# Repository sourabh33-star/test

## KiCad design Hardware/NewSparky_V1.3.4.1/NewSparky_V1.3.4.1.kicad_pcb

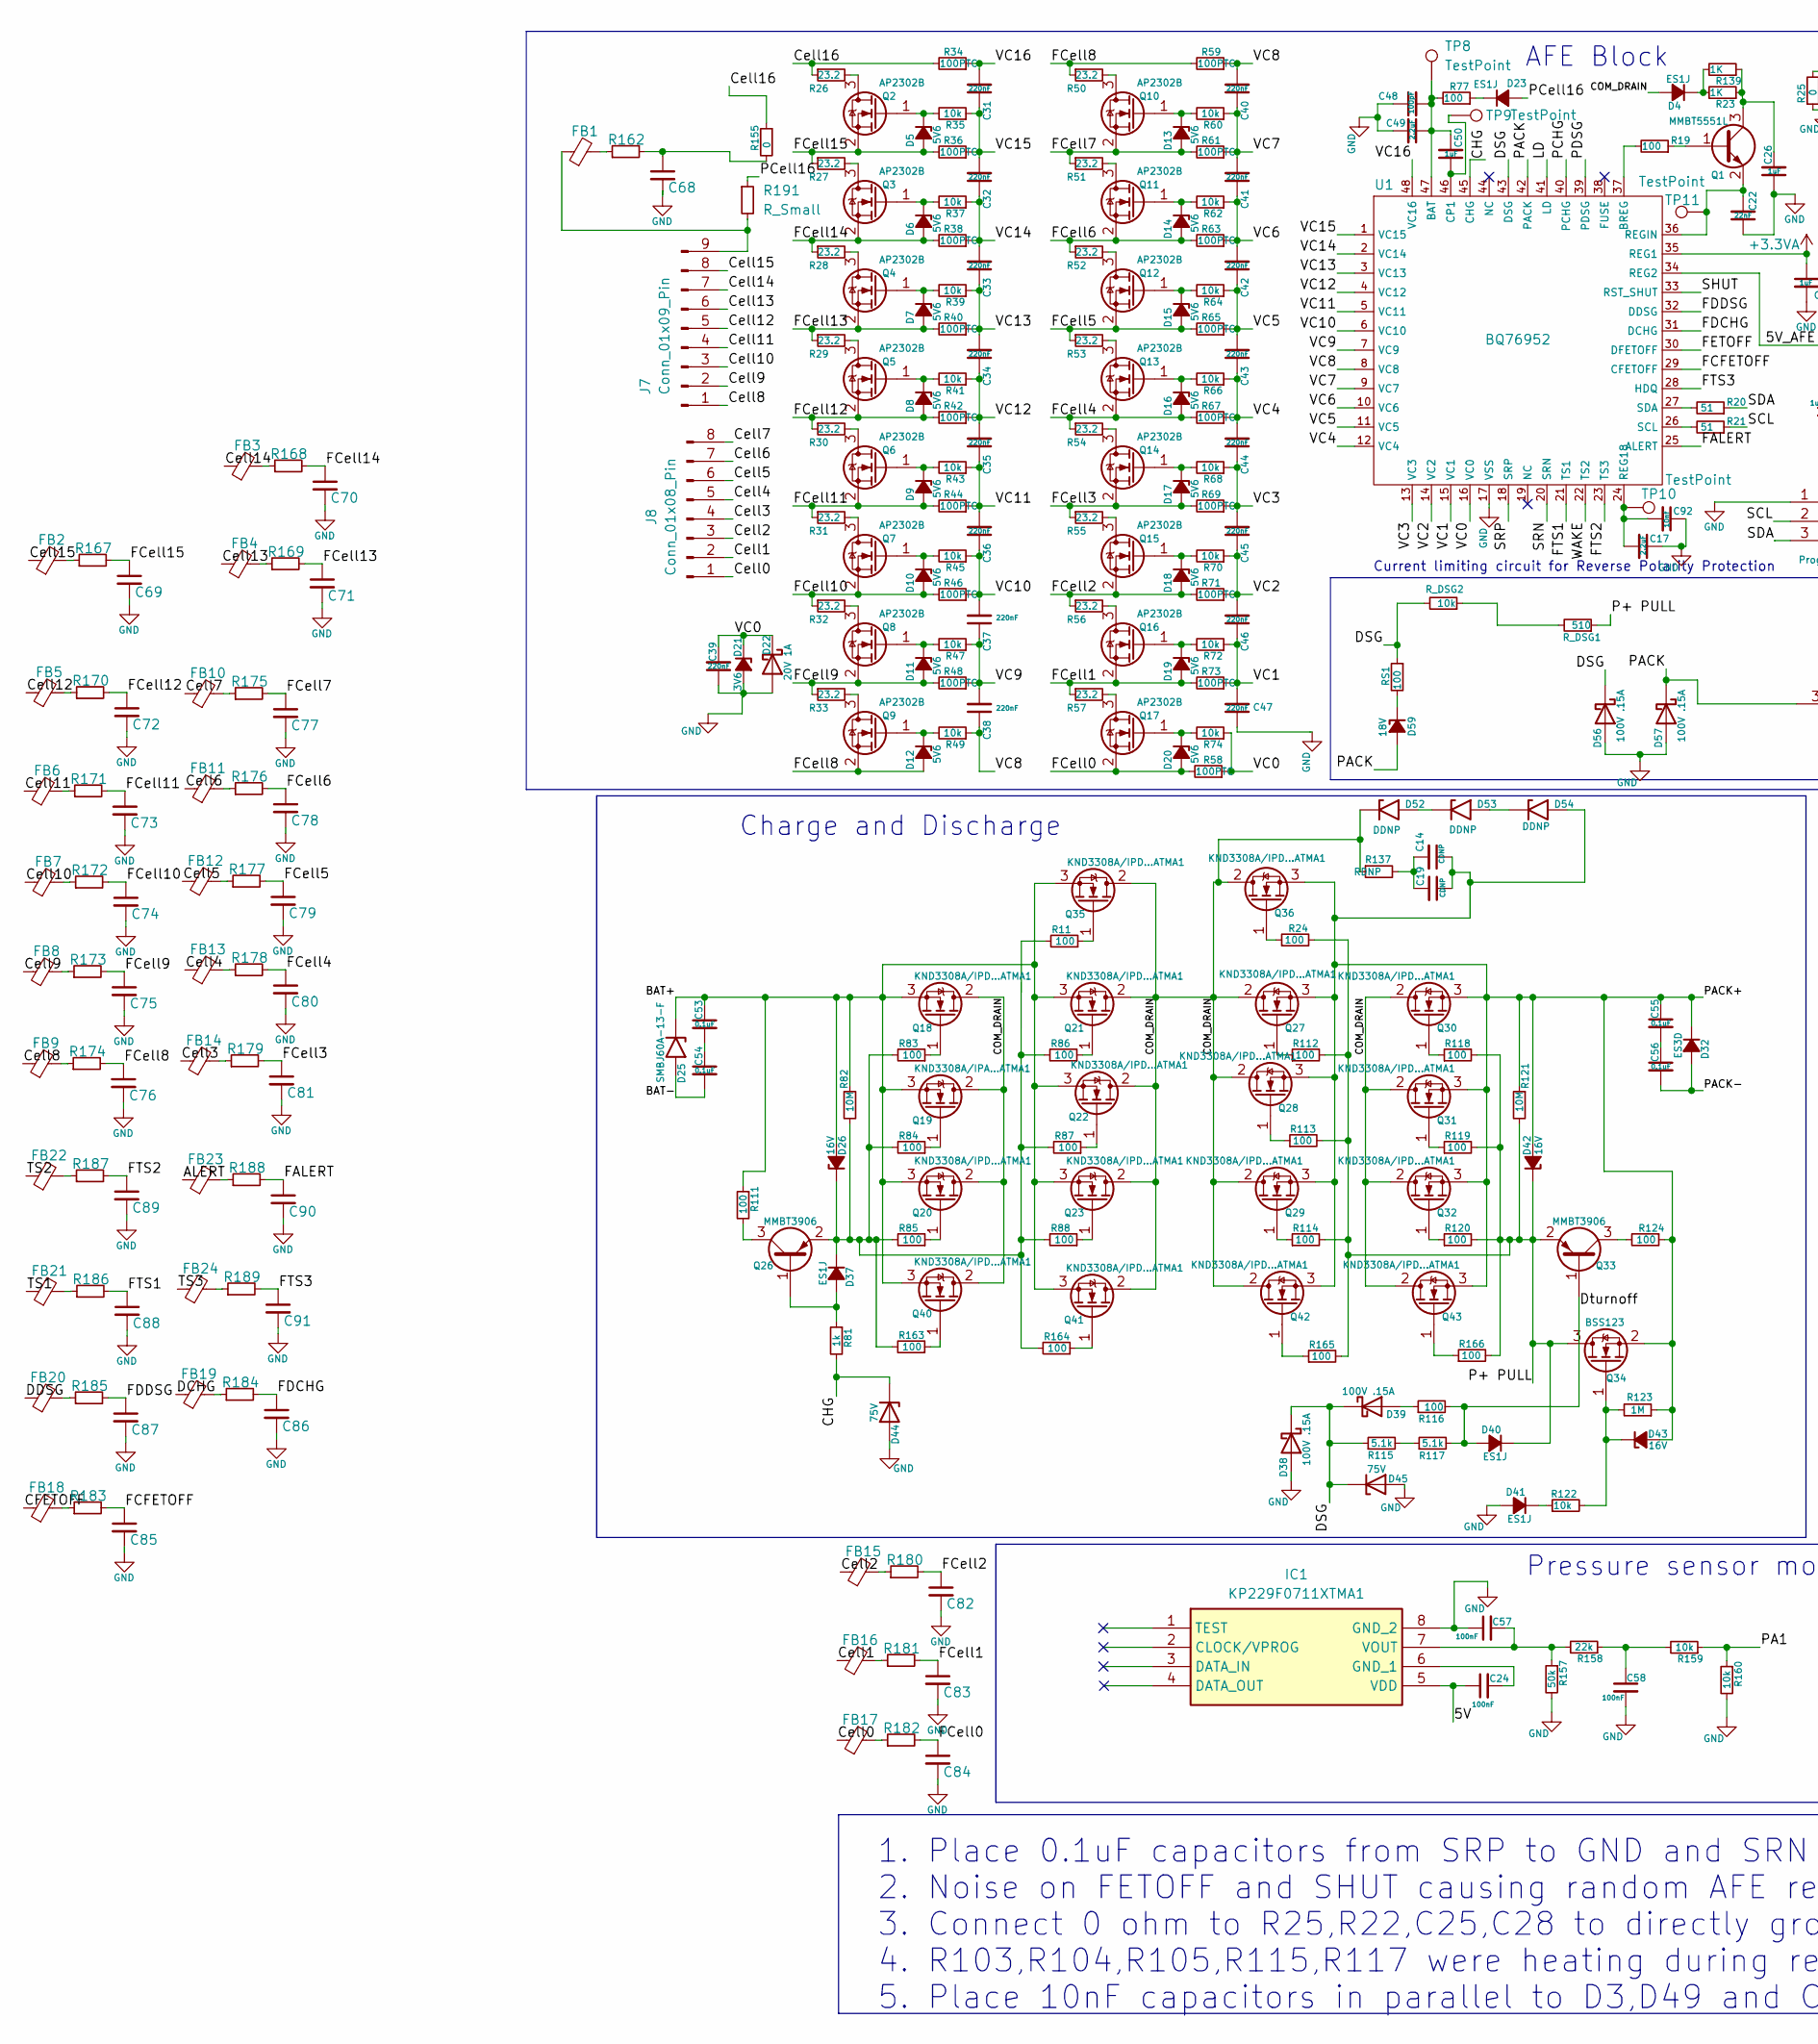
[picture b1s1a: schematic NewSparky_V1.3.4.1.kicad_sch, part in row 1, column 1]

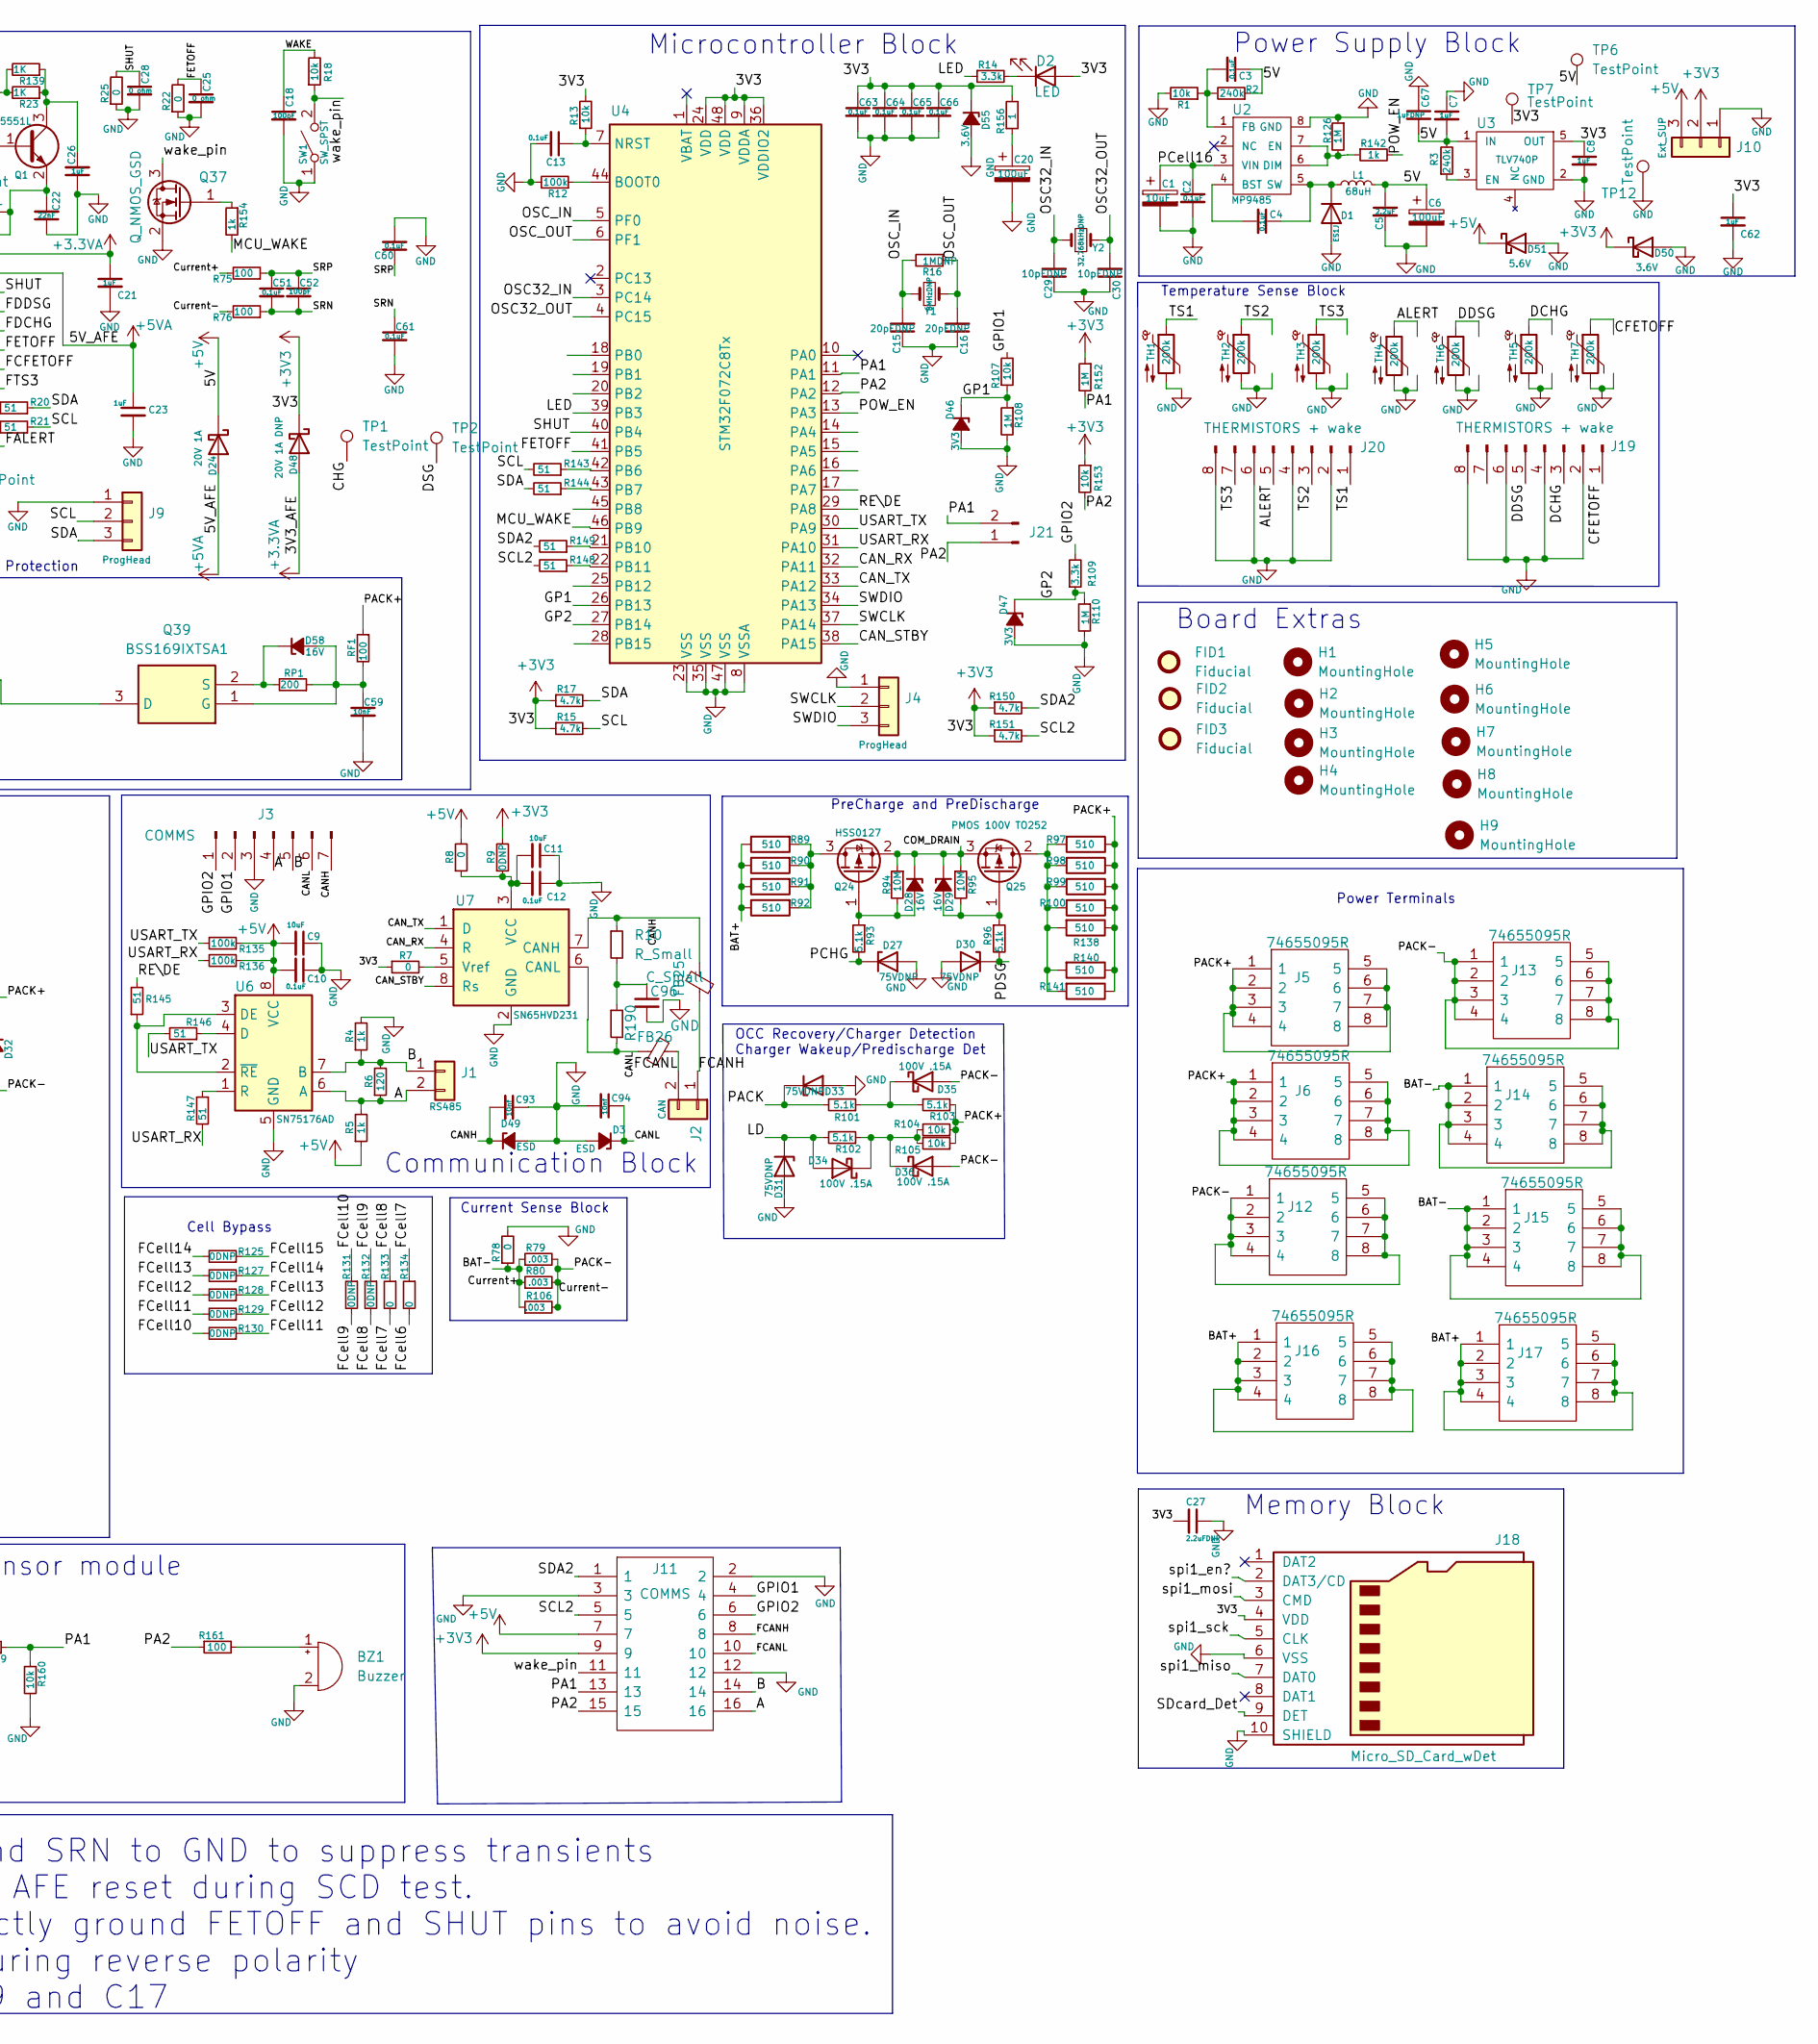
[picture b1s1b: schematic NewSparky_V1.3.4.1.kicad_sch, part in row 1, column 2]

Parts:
BZ1: Buzzer; Buzzer_12x9.5RM7.6
C1: 10uF
C2, C3, C4, C10, C12, C13, C51, C53, C54, C55, C56, C60, C61, C63, C64, C65, C66: 0.1uF; C_0603_1608Metric
C5, C17: 2.2uF; C_0603_1608Metric
C6, C20: 100uF; CP_Radial_D5.0mm_P2.00mm
C7, C8, C21, C23, C62: 1uF; C_0603_1608Metric
C9, C11: 10uF; C_0603_1608Metric
C14, C19: CDNP; C_1206_3216Metric
C15, C16: 20pFDNP; C_0603_1608Metric
C18, C48, C52: 100pF; C_0603_1608Metric
C22: 22nF; C_0603_1608Metric
C24, C57, C58: 100nF; C_0603_1608Metric
C25, C28: 0 ohm; C_0603_1608Metric
C26, C50: 1uF; C_1206_3216Metric
C27: 2.2uFDNP; C_1206_3216Metric
C29, C30: 10pFDNP; C_0603_1608Metric
C31, C32, C33, C34, C35, C36, C37, C38, C39, C40, C41, C42, C43, C44, C45, C46, C47: 220nF; C_0603_1608Metric
C49: 2.2uF; C_1206_3216Metric
C59: 10nF; C_0603_1608Metric
C67: 1uFDNP; C_0603_1608Metric
C68, C69, C70, C71, C72, C73, C74, C75, C76, C77, C78, C79, C80, C81, C82, C83, C84, C96: C_Small; C_0603_1608Metric
C85, C86, C87, C88, C89, C90, C91: C_Small; C_1206_3216Metric
C92, C93, C94: 10nf; C_0603_1608Metric
D1, D4, D23, D37, D40, D41: ES1J; D_SOD-123
D2: LED; LED_0603_1608Metric
D3, D49: ESD; D_SOD-523
D5, D6, D7, D8, D9, D10, D11, D12, D13, D14, D15, D16, D17, D18, D19, D20: 5V6; D_SOD-323
D21: 3V6; D_SOD-323
D22, D24: 20V 1A; D_SOD-123
D25: SMBJ60A-13-F; D_SMC
D26, D28, D29, D42, D43, D58: 16V; D_SOD-123
D27, D30, D31, D33: 75VDNP; D_SOD-123
D32: ES3D; D_SMC
D34, D35, D36, D38, D39, D56, D57: 100V .15A; D_SOD-123
D44, D45: 75V; D_SOD-123
D46, D47: 3V3; D_SOD-323
D48: 20V 1A DNP; D_SOD-123
D50, D55: 3.6V; D_SOD-123
D51: 5.6V; D_SOD-123
D52, D53, D54: DDNP; D_SMA
D59: 18V; D_SOD-123
FB1, FB2, FB3, FB4, FB5, FB6, FB7, FB8, FB9, FB10, FB11, FB12, FB13, FB14, FB15, FB16, FB17, FB18, FB19, FB20, FB21, FB22, FB23, FB24, FB25, FB26: FerriteBead_Small; L_0603_1608Metric
FID1, FID2, FID3: Fiducial; Fiducial_1mm_Mask2mm
H1, H2, H3, H4, H5, H6, H7, H8, H9: MountingHole; MountingHole_3.2mm_M3_DIN965
IC1: KP229F0711XTMA1; Manufacturer_Part_Number KP229F0711XTMA1; Mouser Part Number 726-KP229F0711XTMA1
J1: RS485; JST_XH_S2B-XH-A-1_1x02_P2.50mm_Horizontal
J2: CAN; JST_XH_S2B-XH-A-1_1x02_P2.50mm_Horizontal
J3: COMMS; JST_XH_S7B-XH-A-1_1x07_P2.50mm_Horizontal
J4, J9: ProgHead; PinHeader_1x03_P2.54mm_Vertical
J5, J6, J12, J13, J14, J15, J16, J17: 74655095R; Manufacturer_Part_Number 74650094; Mouser Part Number 710-74650094
J7: Conn_01x09_Pin; 559350910
J8: Conn_01x08_Pin; 559350810
J10: Ext_SUP; PinHeader_1x03_P2.54mm_Vertical
J11: COMMS; S16BPUDSS1LFSN; Manufacturer_Part_Number 501876-1640; Mouser Part Number 538-501876-1640
J18: Micro_SD_Card_wDet; SHOU HAN TF PUSH
J19, J20: THERMISTORS + wake; CONN_S08B-PUDSS-1_JST
J21: Conn_01x02_Pin; PinSocket_1x02_P2.54mm_Vertical
L1: 68uH; L_Taiyo-Yuden_NR-40xx
Q1: MMBT5551L; SOT-23
Q2, Q3, Q4, Q5, Q6, Q7, Q8, Q9, Q10, Q11, Q12, Q13, Q14, Q15, Q16, Q17: AP2302B; SOT-23
Q18, Q20, Q21, Q22, Q23, Q27, Q28, Q29, Q30, Q31, Q32, Q35, Q36, Q40, Q41, Q42, Q43: KND3308A/IPD...ATMA1; TO-252-2
Q19: KND3308A/IPA...ATMA1; TO-252-2
Q24: HSS0127; SOT-23
Q25: PMOS 100V TO252; TO-252-2
Q26, Q33: MMBT3906; SOT-23
Q34: BSS123; SOT-23
Q37: Q_NMOS_GSD; SOT-23
Q39: BSS169IXTSA1; SOT95P237X112-3N; Manufacturer_Part_Number BSS169IXTSA1; Mouser Part Number 726-BSS169IXTSA1
R1, R13, R18, R35, R37, R39, R41, R43, R45, R47, R49, R60, R62, R64, R66, R68, R70, R72, R74, R107, R122, R153, R159, R160: 10k; R_0603_1608Metric
R2, R3: 240k; R_0603_1608Metric
R4, R5, R81, R142, R154: 1k; R_0603_1608Metric
R6: 120; R_0603_1608Metric
R7, R8, R22, R25, R133, R134, R155: 0; R_0603_1608Metric
R9, R125, R127, R128, R129, R130, R131, R132: 0DNP; R_0603_1608Metric
R10, R162, R167, R168, R169, R170, R171, R172, R173, R174, R175, R176, R177, R178, R179, R180, R181, R182, R183, R184, R185, R186, R187, R188, R189, R190, R191: R_Small; R_0603_1608Metric
R11, R19, R24, R75, R76, R77, R83, R84, R85, R86, R87, R88, R111, R112, R113, R114, R116, R118, R119, R120, R124, R161, R163, R164, R165, R166: 100; R_0603_1608Metric
R12, R135, R136: 100k; R_0603_1608Metric
R14, R109: 3.3k; R_0603_1608Metric
R15, R17, R150, R151: 4.7k; R_0603_1608Metric
R16: 1MDNP; R_0603_1608Metric
R20, R21, R143, R144, R145, R146, R147, R148, R149: 51; R_0603_1608Metric
R23, R139: 1K; R_1206_3216Metric
R26, R27, R28, R29, R30, R31, R32, R33, R50, R51, R52, R53, R54, R55, R56, R57: 23.2; R_2512_6332Metric
R34, R36, R38, R40, R42, R44, R46, R48, R58, R59, R61, R63, R65, R67, R69, R71, R73: 100PTC; R_0603_1608Metric
R78: 0; R_1206_3216Metric
R79, R80, R106: .003; RESC15078X50N
R82, R94, R95, R121: 10M; R_0603_1608Metric
R89, R90, R91, R92, R97, R98, R99, R100, R138, R140, R141: 510; R_2512_6332Metric_Pad1.40x3.35mm_HandSolder
R93, R96, R101, R102: 5.1k; R_0603_1608Metric
R103, R115, R117: 5.1k; R_1206_3216Metric
R104, R105: 10k; R_1206_3216Metric
R108, R110, R123, R126, R152: 1M; R_0603_1608Metric
R137: RDNP; R_1206_3216Metric
R156: 1; R_0603_1608Metric
R157: 50k; R_0603_1608Metric
R158: 22k; R_0603_1608Metric
RF1: 100; R_0603_1608Metric
RP1: 200; R_0603_1608Metric
RS1: 100; R_0603_1608Metric
R_DSG1: 510; R_1206_3216Metric
R_DSG2: 10k; R_1206_3216Metric
SW1: SW_SPST; PinHeader_1x02_P2.54mm_Vertical
TH1, TH2, TH3, TH4, TH5, TH6, TH7: 200k; JST_EH_S2B-EH_1x02_P2.50mm_Horizontal
TP1, TP2: TestPoint; TestPoint_THTPad_1.0x1.0mm_Drill0.5mm
TP6, TP7, TP8, TP9, TP10, TP11, TP12: TestPoint; TestPoint_THTPad_2.0x2.0mm_Drill1.0mm
U1: BQ76952; QFP50P900X900X120-48N
U2: MP9485; SOIC-8-1EP_3.9x4.9mm_P1.27mm_EP2.41x3.3mm
U3: TLV740P; SOT-23-5
U4: STM32F072C8Tx; QFP50P900X900X160-48N
U6: SN75176AD; SOIC-8_3.9x4.9mm_P1.27mm
U7: SN65HVD231; SOIC-8_3.9x4.9mm_P1.27mm
Y1: 8MHzDNP; Crystal_SMD_HC49-SD
Y2: 32.768kHzDNP; Crystal_Round_D3.0mm_Vertical

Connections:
+3.3VA: C21.1, D48.2 (A), U1.35 (REG1)
+3V3: C8.1, C27.2, C62.1, C63.1, C64.1, C65.1, C66.1, D2.2 (A), D48.1 (K), D50.1 (K), D55.1 (K), J10.2, J11.9, J18.4 (VDD), R7.1, R9.2, R13.2, R15.1, R17.1, R150.1, R151.1, R152.1, R153.1, R156.2, TP7.1, U3.5 (OUT), U4.9 (VDDA), U4.24 (VDD), U4.36 (VDDIO2), U4.48 (VDD)
+5V: C3.1, C5.1, C6.1, C7.2, C9.2, C10.2, C24.1, C67.2, D24.1 (K), D51.1 (K), IC1.5 (VDD), J10.3, J11.7, L1.2, R2.1, R3.2, R5.1, R8.2, R135.1, R136.1, TP6.1, U3.1 (IN), U6.8 (VCC)
+5VA: C23.1, D24.2 (A), U1.34 (REG2)
/A: J1.2, J3.4, J11.16, R5.2, R6.1, U6.6 (A)
/ALERT: FB23.1, J20.5, TH4.1
/B: J1.1, J3.5, J11.14, R4.1, R6.2, U6.7 (B)
/BAT+: C53.1, D25.1 (A1), D26.2 (A), J16.1, J16.2, J16.3, J16.4, J16.5, J16.6, J16.7, J16.8, J17.1, J17.2, J17.3, J17.4, J17.5, J17.6, J17.7, J17.8, Q18.3 (S), Q19.3 (S), Q20.3 (S), Q21.3 (S), Q22.3 (S), Q23.3 (S), Q35.3 (S), Q40.3 (S), Q41.3 (S), R82.1, R89.1, R90.1, R91.1, R92.1, R111.1; also elsewhere on the board
/CANH: C93.2, D49.1 (K), FB25.2, J3.7, R10.1, U7.7 (CANH)
/CANL: C94.1, D3.1 (K), FB26.2, J3.6, R190.2, U7.6 (CANL)
/CAN_RX: U4.32 (PA11), U7.4 (R)
/CAN_STBY: U4.38 (PA15), U7.8 (Rs)
/CAN_TX: U4.33 (PA12), U7.1 (D)
/CFETOFF: FB18.1, J19.1, TH7.1
/CHG: D44.1 (K), R81.2, TP1.1, U1.45 (CHG)
/COM_DRAIN: D4.2 (A), D28.1 (K), D29.1 (K), D52.1 (A1), Q18.2 (D), Q19.2 (D), Q20.2 (D), Q21.2 (D), Q22.2 (D), Q23.2 (D), Q24.2 (S), Q25.3 (S), Q27.2 (D), Q28.2 (D), Q29.2 (D), Q30.2 (D), Q31.2 (D), Q32.2 (D), Q35.2 (D), Q36.2 (D), Q40.2 (D), Q41.2 (D), Q42.2 (D), Q43.2 (D), R94.1, R95.1, R137.1
/Cell0: FB17.1, J8.1
/Cell1: FB16.1, J8.2
/Cell2: FB15.1, J8.3
/Cell3: FB14.1, J8.4
/Cell4: FB13.1, J8.5
/Cell5: FB12.1, J8.6
/Cell6: FB11.1, J8.7
/Cell7: FB10.1, J8.8
/Cell8: FB9.1, J7.1
/Cell9: FB8.1, J7.2
/Cell10: FB7.1, J7.3
/Cell11: FB6.1, J7.4
/Cell12: FB5.1, J7.5
/Cell13: FB4.1, J7.6
/Cell14: FB3.1, J7.7
/Cell15: FB2.1, J7.8
/Cell16: R26.1, R34.2, R155.1
/DCHG: FB19.1, J19.3, TH5.1
/DDSG: FB20.1, J19.5, TH6.1
/DSG: D38.1 (K), D39.1 (K), D45.1 (K), D56.1 (K), R115.1, RS1.1, R_DSG2.2, TP2.1, U1.43 (DSG)
/Dturnoff: D40.2 (A), Q33.1 (B), R116.2, R117.2
/FALERT: C90.1, R188.2, U1.25 (ALERT)
/FCANH: FB25.1, J2.1, J11.8
/FCANL: FB26.1, J2.2, J11.10
/FCFETOFF: C85.1, R183.2, U1.29 (CFETOFF)
/FCell0: C84.1, D20.2 (A), Q17.2 (S), R58.2, R182.2
/FCell1: C83.1, D19.2 (A), Q16.2 (S), R57.1, R73.2, R181.2
/FCell2: C82.1, D18.2 (A), Q15.2 (S), R56.1, R71.2, R180.2
/FCell3: C81.1, D17.2 (A), Q14.2 (S), R55.1, R69.2, R179.2
/FCell4: C80.1, D16.2 (A), Q13.2 (S), R54.1, R67.2, R178.2
/FCell5: C79.1, D15.2 (A), Q12.2 (S), R53.1, R65.2, R177.2
/FCell6: C78.1, D14.2 (A), Q11.2 (S), R52.1, R63.2, R134.2, R176.2
/FCell7: C77.1, D13.2 (A), Q10.2 (S), R51.1, R61.2, R133.2, R134.1, R175.2
/FCell8: C76.1, D12.2 (A), Q9.2 (S), R50.1, R59.2, R132.2, R133.1, R174.2
/FCell9: C75.1, D11.2 (A), Q8.2 (S), R33.1, R48.2, R131.2, R132.1, R173.2
/FCell10: C74.1, D10.2 (A), Q7.2 (S), R32.1, R46.2, R130.2, R131.1, R172.2
/FCell11: C73.1, D9.2 (A), Q6.2 (S), R31.1, R44.2, R129.2, R130.1, R171.2
/FCell12: C72.1, D8.2 (A), Q5.2 (S), R30.1, R42.2, R128.2, R129.1, R170.2
/FCell13: C71.1, D7.2 (A), Q4.2 (S), R29.1, R40.2, R127.2, R128.1, R169.2
/FCell14: C70.1, D6.2 (A), Q3.2 (S), R28.1, R38.2, R125.2, R127.1, R168.2
/FCell15: C69.1, D5.2 (A), Q2.2 (S), R27.1, R36.2, R125.1, R167.2
/FDCHG: C86.1, R184.2, U1.31 (DCHG)
/FDDSG: C87.1, R185.2, U1.32 (DDSG)
/FETOFF: C25.1, R22.2, U1.30 (DFETOFF), U4.41 (PB5)
/FTS1: C88.1, R186.2, U1.21 (TS1)
/FTS2: C89.1, R187.2, U1.23 (TS3)
/FTS3: C91.1, R189.2, U1.28 (HDQ)
/GP1: D46.1 (K), R107.1, R108.1, U4.26 (PB13)
/GP2: D47.1 (K), R109.1, R110.1, U4.27 (PB14)
/GPIO1: J3.2, J11.4, R107.2
/GPIO2: J3.1, J11.6, R109.2
/LD: D31.1 (K), D34.2 (A), R102.2, U1.41 (LD)
/LED: R14.1, U4.39 (PB3)
/MCU_WAKE: R154.2, U4.46 (PB9)
/OSC32_IN: C29.2, U4.3 (PC14), Y2.1
/OSC32_OUT: C30.2, U4.4 (PC15), Y2.2
/OSC_IN: C15.2, R16.2, U4.5 (PF0), Y1.1
/OSC_OUT: C16.2, R16.1, U4.6 (PF1), Y1.2
/P+ PULL: D40.1 (K), D42.1 (K), Q33.2 (E), Q34.3 (D), R24.2, R112.2, R113.2, R114.2, R118.2, R119.2, R120.2, R121.2, R165.2, R166.2, R_DSG1.1
/PA1: J11.13, J21.2, R152.2, R159.1, R160.1, U4.11 (PA1)
/PA2: J11.15, J21.1, R153.2, R161.1, U4.12 (PA2)
/PACK: D33.1 (K), D57.1 (K), D59.2 (A), Q39.3 (D), R101.2, U1.42 (PACK)
/PACK+: C14.1, C19.1, C55.1, D32.1 (K), D42.2 (A), D43.2 (A), D54.2 (A2), J5.1, J5.2, J5.3, J5.4, J5.5, J5.6, J5.7, J5.8, J6.1, J6.2, J6.3, J6.4, J6.5, J6.6, J6.7, J6.8, Q27.3 (S), Q28.3 (S), Q29.3 (S), Q30.3 (S), Q31.3 (S), Q32.3 (S), Q34.2 (S), Q36.3 (S), Q42.3 (S), Q43.3 (S), R97.1, R98.1, R99.1, R100.1, R103.1, R104.1, R105.1, R121.1, R123.1, R124.1, R138.1, R140.1, R141.1, RF1.1
/PCHG: D27.1 (K), R93.2, U1.40 (PCHG)
/PCell16: C1.1, C2.1, D23.2 (A), R191.1, U2.3 (VIN)
/PDSG: D30.1 (K), R96.2, U1.39 (PDSG)
/POW_EN: R142.2, U4.13 (PA3)
/RE\DE: R145.2, U4.29 (PA8)
/SCL: J9.2, R15.2, R21.1, R143.2
/SCL2: J11.5, R148.2, R151.2
/SDA: J9.3, R17.2, R20.1, R144.2
/SDA2: J11.1, R149.2, R150.2
/SDcard_Det: J18.9 (DET)
/SHUT: C28.1, R25.2, U1.33 (RST_SHUT), U4.40 (PB4)
/SRN: C51.2, C52.2, C61.1, R76.1, U1.20 (SRN)
/SRP: C51.1, C52.1, C60.1, R75.1, U1.18 (SRP)
/SWCLK: J4.2, U4.37 (PA14)
/SWDIO: J4.3, U4.34 (PA13)
/TS1: FB21.1, J20.1, TH1.1
/TS2: FB22.1, J20.3, TH2.1
/TS3: FB24.1, J20.7, TH3.1
/USART_RX: R136.2, R147.2, U4.31 (PA10)
/USART_TX: R135.2, R146.2, U4.30 (PA9)
/VC0: C39.2, D21.1 (K), D22.1 (K), R58.1, R74.1, U1.16 (VC0)
/VC1: C46.1, C47.2, R72.1, R73.1, U1.15 (VC1)
/VC2: C45.1, C46.2, R70.1, R71.1, U1.14 (VC2)
/VC3: C44.1, C45.2, R68.1, R69.1, U1.13 (VC3)
/VC4: C43.1, C44.2, R66.1, R67.1, U1.12 (VC4)
/VC5: C42.1, C43.2, R64.1, R65.1, U1.11 (VC5)
/VC6: C41.1, C42.2, R62.1, R63.1, U1.10 (VC6)
/VC7: C40.1, C41.2, R60.1, R61.1, U1.9 (VC7)
/VC8: C38.1, C40.2, R49.1, R59.1, U1.8 (VC8)
/VC9: C37.1, C38.2, R47.1, R48.1, U1.7 (VC9)
/VC10: C36.1, C37.2, R45.1, R46.1, U1.6 (VC10)
/VC11: C35.1, C36.2, R43.1, R44.1, U1.5 (VC11)
/VC12: C34.1, C35.2, R41.1, R42.1, U1.4 (VC12)
/VC13: C33.1, C34.2, R39.1, R40.1, U1.3 (VC13)
/VC14: C32.1, C33.2, R37.1, R38.1, U1.2 (VC14)
/VC15: C31.1, C32.2, R35.1, R36.1, U1.1 (VC15)
/VC16: C31.2, R34.1, U1.48 (VC16)
/WAKE: C18.1, R18.2, U1.22 (TS2)
/spi1_en?: J18.2 (DAT3/CD)
/spi1_miso: J18.7 (DAT0)
/spi1_mosi: J18.3 (CMD)
/spi1_sck: J18.5 (CLK)
/wake_pin: J11.11, Q37.3 (D), R18.1, SW1.2 (B)
GND: BZ1.2 (+), C1.2, C2.2, C5.2, C6.2, C7.1, C8.2, C9.1, C10.1, C11.1, C12.1, C13.2, C15.1, C16.1, C17.1, C18.2, C20.2, C21.2, C22.1, C23.2, C25.2, C26.1, C27.1, C28.2, C29.1, C30.1, C39.1, C47.1, C48.1, C49.2, C57.1, C58.2, C59.2, C60.2, C61.2, C62.2, C63.2, C64.2, C65.2, C66.2, C67.1, C68.2, C69.2, C70.2, C71.2, C72.2, C73.2, C74.2, C75.2, C76.2, C77.2, C78.2, C79.2, C80.2, C81.2, C82.2, C83.2, C84.2, C85.2, C86.2, C87.2, C88.2, C89.2, C90.2, C91.2, C92.1, C93.1, C94.2, C96.2, D1.2 (A), D3.2 (A), D21.2 (A), D22.2 (A), D27.2 (A), D30.2 (A), D31.2 (A), D33.2 (A), D38.2 (A), D41.2 (A), D44.2 (A), D45.2 (A), D46.2 (A), D47.2 (A), D49.2 (A), D50.2 (A), D51.2 (A), D55.2 (A), D56.2 (A), D57.2 (A), IC1.8 (GND_2), J3.3, J4.1, J9.1, J10.1, J11.2, J11.3, J11.12, J18.6 (VSS), J18.10 (SHIELD), J19.2, J19.4, J19.6, J19.8, J20.2, J20.4, J20.6, J20.8, Q37.2 (S), R1.2, R4.2, R12.2, R22.1, R25.1, R78.2, R108.2, R110.2, R126.1, R157.2, R160.2, SW1.1 (A), TH1.2, TH2.2, TH3.2, TH4.2, TH5.2, TH6.2, TH7.2, TP12.1, U1.17 (VSS), U2.8 (GND), U2.9 (GND), U3.2 (GND), U4.8 (VSSA), U4.23 (VSS), U4.35 (VSS), U4.47 (VSS), U6.5 (GND), U7.2 (GND)
unnamed: BZ1.1 (-), R161.2
unnamed: C14.2, C19.2, R137.2
unnamed: C20.1, R156.1
unnamed: C53.2, C54.1
unnamed: C55.2, C56.1
unnamed: C58.1, R158.1, R159.2
unnamed: C68.1, R155.2, R162.2
unnamed: C96.1, R10.2, R190.1
unnamed: C4.1, D1.1 (K), L1.1, U2.5 (SW)
unnamed: D2.1 (K), R14.2
unnamed: D4.1 (K), R23.2, R139.2
unnamed: D5.1 (K), Q2.1 (G), R35.2
unnamed: D6.1 (K), Q3.1 (G), R37.2
unnamed: D7.1 (K), Q4.1 (G), R39.2
unnamed: D8.1 (K), Q5.1 (G), R41.2
unnamed: D9.1 (K), Q6.1 (G), R43.2
unnamed: D10.1 (K), Q7.1 (G), R45.2
unnamed: D11.1 (K), Q8.1 (G), R47.2
unnamed: D12.1 (K), Q9.1 (G), R49.2
unnamed: D13.1 (K), Q10.1 (G), R60.2
unnamed: D14.1 (K), Q11.1 (G), R62.2
unnamed: D15.1 (K), Q12.1 (G), R64.2
unnamed: D16.1 (K), Q13.1 (G), R66.2
unnamed: D17.1 (K), Q14.1 (G), R68.2
unnamed: D18.1 (K), Q15.1 (G), R70.2
unnamed: D19.1 (K), Q16.1 (G), R72.2
unnamed: D20.1 (K), Q17.1 (G), R74.2
unnamed: D23.1 (K), R77.1
unnamed: D26.1 (K), D37.1 (K), Q26.2 (E), R11.2, R82.2, R83.2, R84.2, R85.2, R86.2, R87.2, R88.2, R163.2, R164.2
unnamed: D29.2 (A), Q25.1 (G), R95.2, R96.1
unnamed: D34.1 (K), D36.1 (K), R102.1, R104.2, R105.2
unnamed: D35.1 (K), R101.1, R103.2
unnamed: D37.2 (A), Q26.1 (B), R81.1
unnamed: D39.2 (A), R116.1
unnamed: D41.1 (K), R122.1
unnamed: D43.1 (K), Q34.1 (G), R122.2, R123.2
unnamed: D52.2 (A2), D53.1 (A1)
unnamed: D53.2 (A2), D54.1 (A1)
unnamed: C59.1, D58.2 (A), Q39.1 (G), RF1.2, RP1.1
unnamed: D58.1 (K), Q39.2 (S), RP1.2
unnamed: D59.1 (K), RS1.2
unnamed: FB1.2, R162.1
unnamed: FB2.2, R167.1
unnamed: FB3.2, R168.1
unnamed: FB4.2, R169.1
unnamed: FB5.2, R170.1
unnamed: FB6.2, R171.1
unnamed: FB7.2, R172.1
unnamed: FB8.2, R173.1
unnamed: FB9.2, R174.1
unnamed: FB10.2, R175.1
unnamed: FB11.2, R176.1
unnamed: FB12.2, R177.1
unnamed: FB13.2, R178.1
unnamed: FB14.2, R179.1
unnamed: FB15.2, R180.1
unnamed: FB16.2, R181.1
unnamed: FB17.2, R182.1
unnamed: FB18.2, R183.1
unnamed: FB19.2, R184.1
unnamed: FB20.2, R185.1
unnamed: FB21.2, R186.1
unnamed: FB22.2, R187.1
unnamed: FB23.2, R188.1
unnamed: FB24.2, R189.1
unnamed: C24.2, IC1.6 (GND_1)
unnamed: C57.2, IC1.7 (VOUT), R157.1, R158.2
unnamed: FB1.1, J7.9, R191.2
unnamed: Q1.1 (B), R19.1
unnamed: C26.2, Q1.3 (C), R23.1, R139.1
unnamed: C22.2, Q1.2 (E), TP11.1, U1.36 (REGIN)
unnamed: Q2.3 (D), R26.2
unnamed: Q3.3 (D), R27.2
unnamed: Q4.3 (D), R28.2
unnamed: Q5.3 (D), R29.2
unnamed: Q6.3 (D), R30.2
unnamed: Q7.3 (D), R31.2
unnamed: Q8.3 (D), R32.2
unnamed: Q9.3 (D), R33.2
unnamed: Q10.3 (D), R50.2
unnamed: Q11.3 (D), R51.2
unnamed: Q12.3 (D), R52.2
unnamed: Q13.3 (D), R53.2
unnamed: Q14.3 (D), R54.2
unnamed: Q15.3 (D), R55.2
unnamed: Q16.3 (D), R56.2
unnamed: Q17.3 (D), R57.2
unnamed: Q18.1 (G), R83.1
unnamed: Q19.1 (G), R84.1
unnamed: Q20.1 (G), R85.1
unnamed: Q21.1 (G), R86.1
unnamed: Q22.1 (G), R87.1
unnamed: Q23.1 (G), R88.1
unnamed: Q24.3 (D), R89.2, R90.2, R91.2, R92.2
unnamed: Q25.2 (D), R97.2, R98.2, R99.2, R100.2, R138.2, R140.2, R141.2
unnamed: Q26.3 (C), R111.2
unnamed: Q27.1 (G), R112.1
unnamed: Q28.1 (G), R113.1
unnamed: Q29.1 (G), R114.1
unnamed: Q30.1 (G), R118.1
unnamed: Q31.1 (G), R119.1
unnamed: Q32.1 (G), R120.1
unnamed: Q33.3 (C), R124.2
unnamed: Q35.1 (G), R11.1
unnamed: Q36.1 (G), R24.1
unnamed: Q37.1 (G), R154.1
unnamed: Q40.1 (G), R163.1
unnamed: Q41.1 (G), R164.1
unnamed: Q42.1 (G), R165.1
unnamed: Q43.1 (G), R166.1
unnamed: R115.2, R117.1
unnamed: R_DSG1.2, R_DSG2.1
unnamed: C48.2, C49.1, C50.2, R77.2, TP8.1, U1.47 (BAT)
unnamed: R19.2, U1.37 (BREG)
unnamed: C50.1, TP9.1, U1.46 (CP1)
unnamed: C17.2, C92.2, TP10.1, U1.24 (REG18)
unnamed: R21.2, U1.26 (SCL)
unnamed: R20.2, U1.27 (SDA)
unnamed: C4.2, U2.4 (BST)
unnamed: R126.2, R142.1, U2.6 (DIM), U2.7 (EN)
unnamed: C3.2, R1.1, R2.2, U2.1 (FB)
unnamed: R3.1, U3.3 (EN)
unnamed: R12.1, U4.44 (BOOT0)
unnamed: C13.1, R13.1, U4.7 (NRST)
unnamed: R143.1, U4.42 (PB6)
unnamed: R144.1, U4.43 (PB7)
unnamed: R149.1, U4.21 (PB10)
unnamed: R148.1, U4.22 (PB11)
unnamed: R146.1, U6.4 (D)
unnamed: R145.1, U6.2 (~RE), U6.3 (DE)
unnamed: R147.1, U6.1 (R)
unnamed: C11.2, C12.2, R8.1, R9.1, U7.3 (VCC)
unnamed: R7.2, U7.5 (Vref)

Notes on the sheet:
OCC Recovery/Charger Detection Charger Wakeup/Predischarge Det
Current limiting circuit for Reverse Polarity Protection
Memory Block
PreCharge and PreDischarge
Communication Block
1. Place 0.1uF capacitors from SRP to GND and SRN to GND to suppress transients 2. Noise on FETOFF and SHUT causing random AFE reset during SCD test. 3. Connect 0 ohm to R25,R22,C25,C28 to directly ground FETOFF and SHUT pins to avoid noise. 4. R103,R104,R105,R115,R117 were heating during reverse p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
Microcontroller Block
Board Extras
Temperature Sense Block
Power Supply Block
AFE Block
Pressure sensor module
Cell Bypass
Charge and Discharge
Current Sense Block
Power Terminals

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
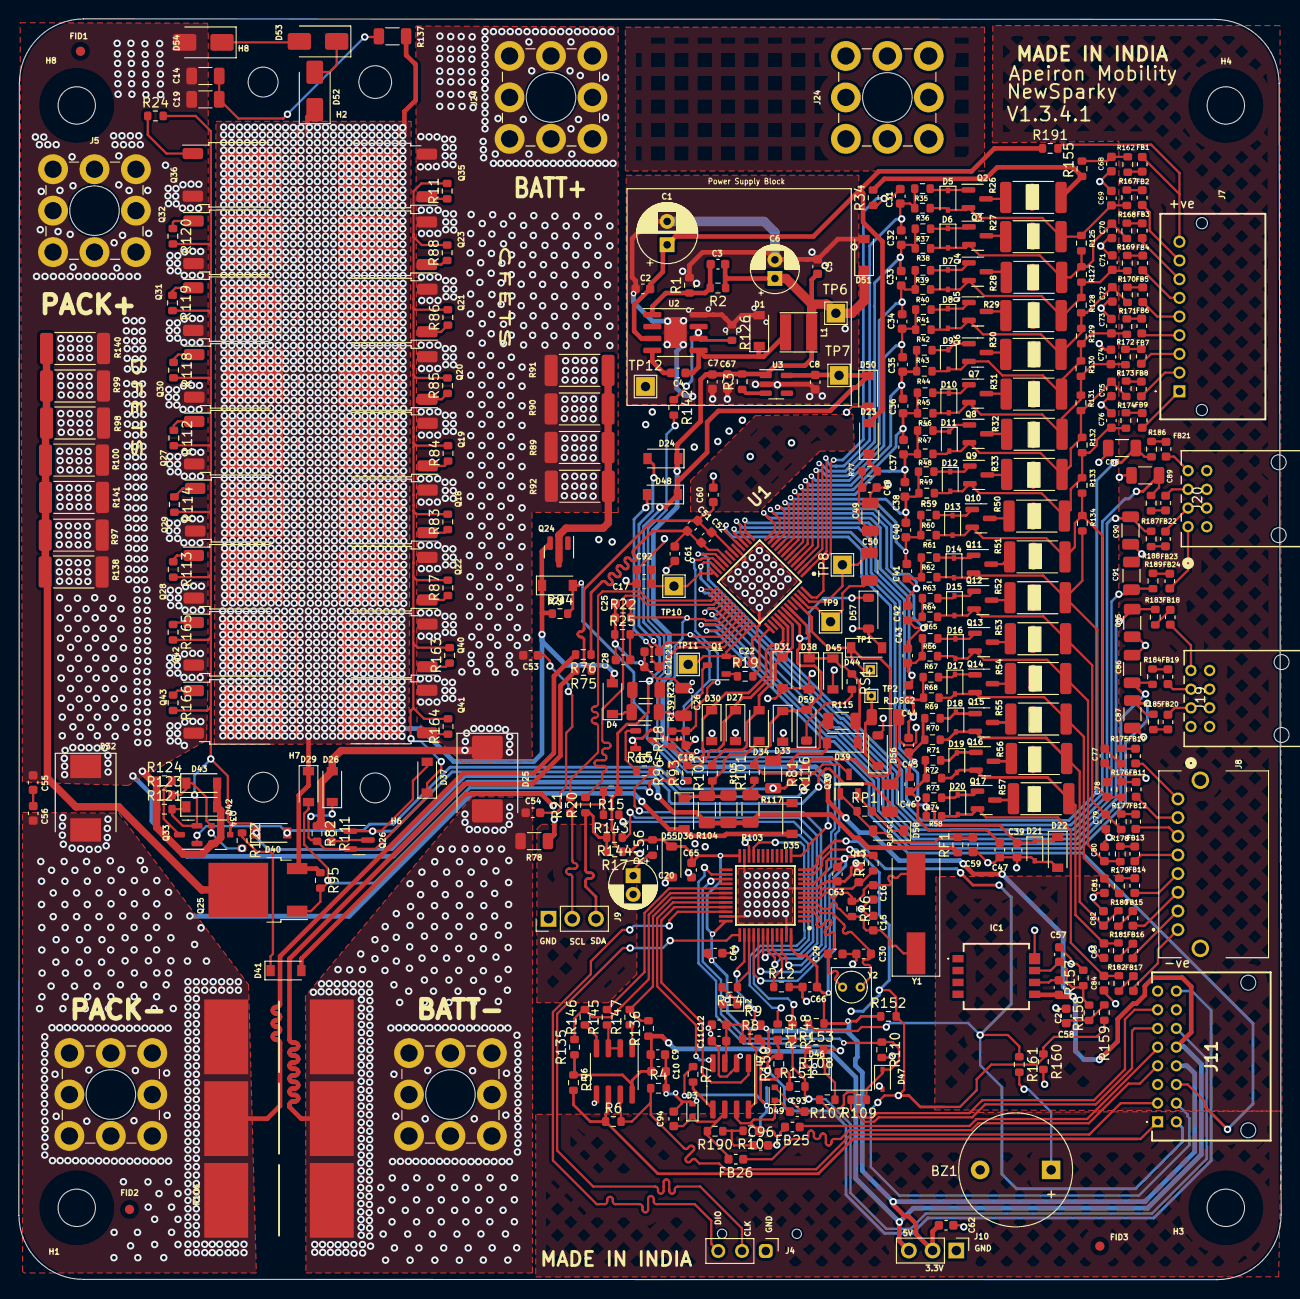
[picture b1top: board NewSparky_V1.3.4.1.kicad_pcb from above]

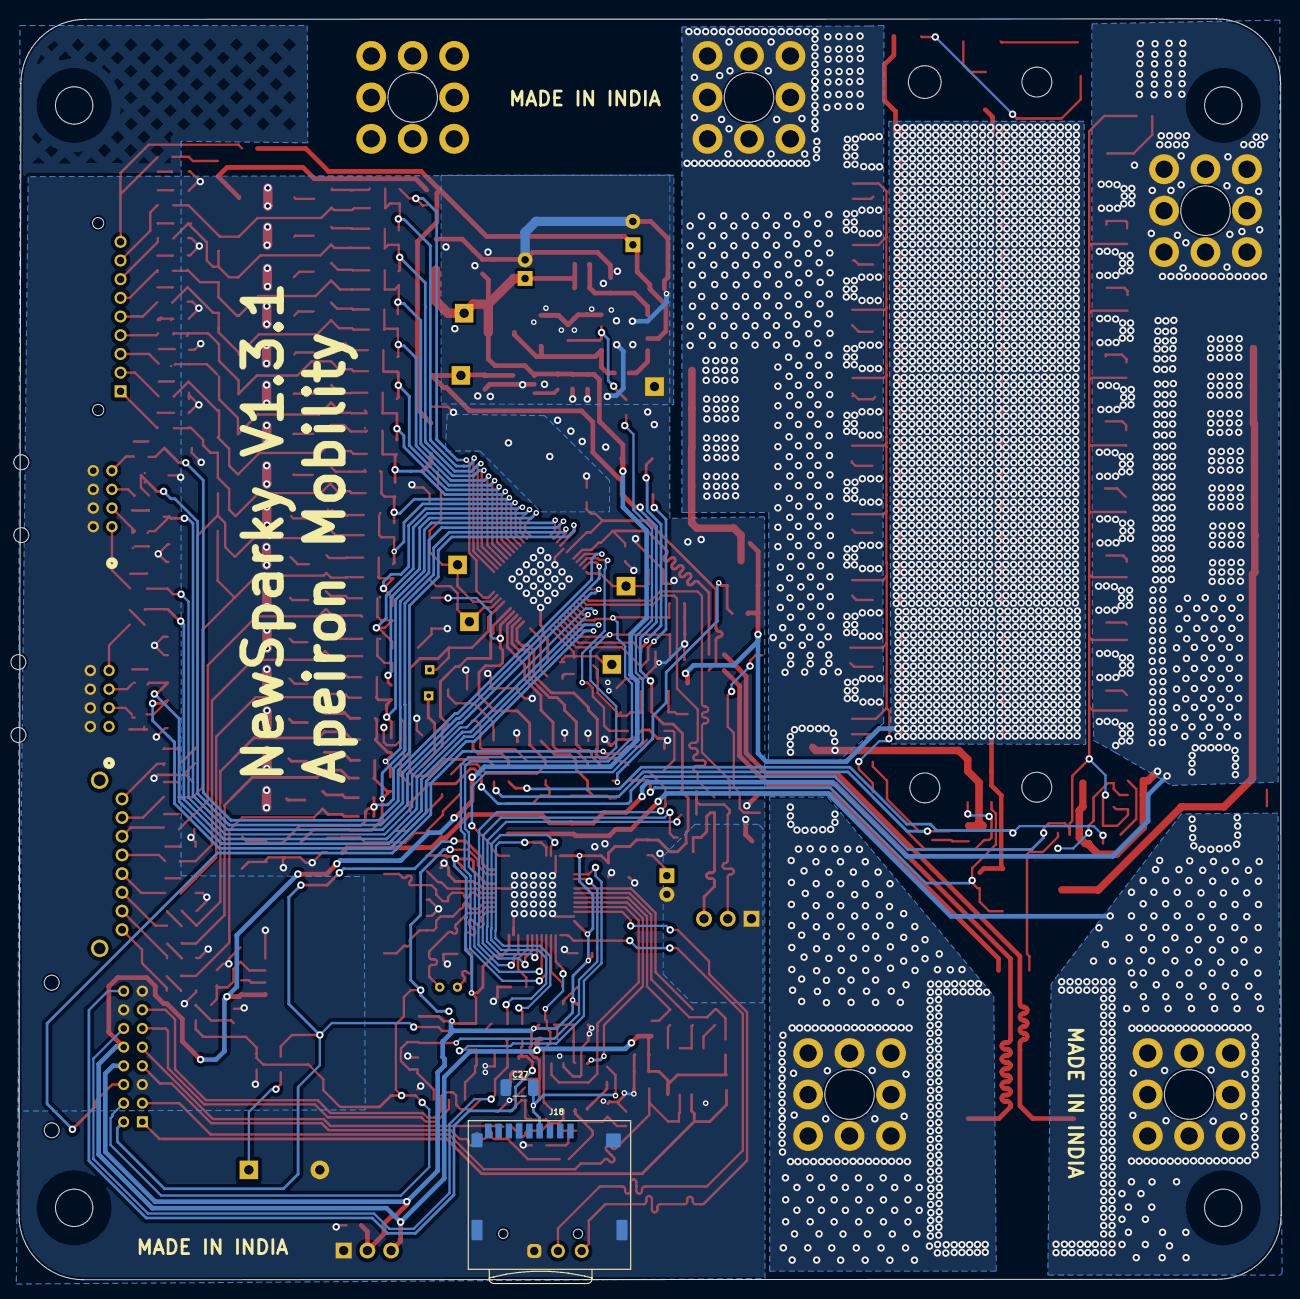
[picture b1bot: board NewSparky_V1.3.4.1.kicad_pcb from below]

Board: 2 copper layers, 135.1 x 135.0 mm, 463 parts (2 on the bottom side), 254 nets.

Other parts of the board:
H8#2: MountingHole; MountingHole_3.2mm_M3_DIN965
J23, J24, J24#2: 74655095R; Wuerth_REDCUBE-THR_WP-THRBU_74655095_THR

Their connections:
/BAT+: J24#2.1; also elsewhere on the board

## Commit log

2025-11-11 Create doc
2025-11-11 Create firmware
2025-11-11 new sparky
